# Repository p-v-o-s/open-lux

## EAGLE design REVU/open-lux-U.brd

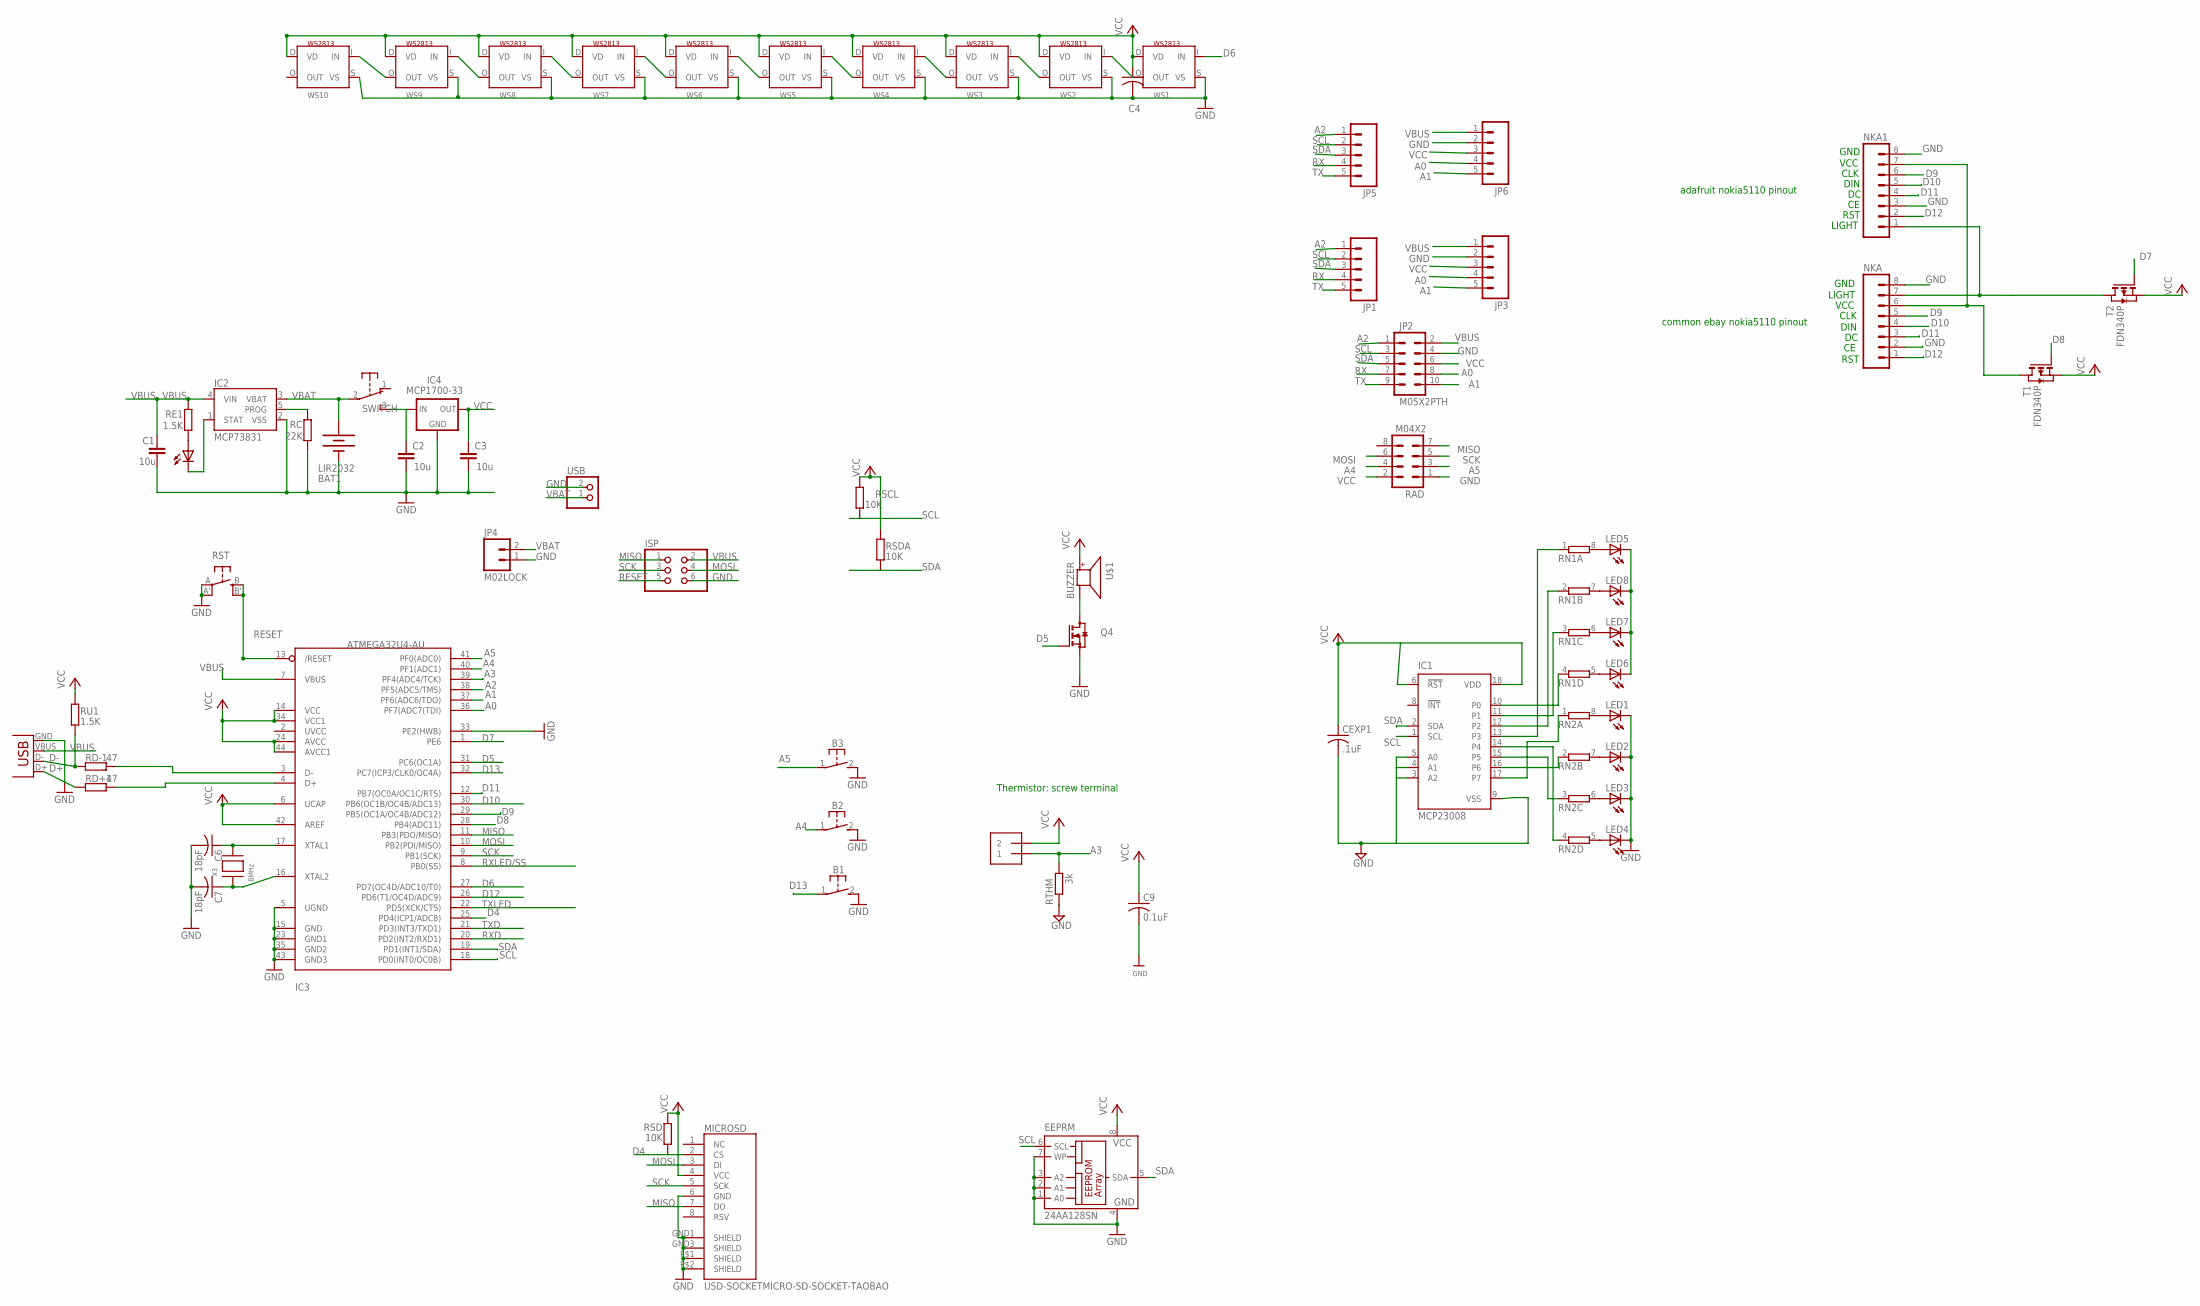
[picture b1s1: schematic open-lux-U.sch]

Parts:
B1, B2, B3: 31-XX; B3F-31XX
BAT1: LIR2032; BATTCOM_20MM_PTH_SMT
C1, C2, C3: 10u; C0805
C4: C-USC0805K; C0805K
C6, C7: 18pF; C0805K
C9: 0.1uF; C0805
CEXP1: .1uF; C0805K
EEPRM: 24AA128SN; SO-08
IC1: MCP23008; SO18W
IC2: MCP73831; SOT23-5
IC3: ATMEGA32U4-AU; TQFP44
IC4: MCP1700-33; SOT23
ISP: PINHD-2X3; 2X03
JP1, JP3, JP5, JP6: M05LOCK; 1X05_LOCK
JP2: M05X2PTH; AVR_ICSP
JP4: M02LOCK; 1X02_LOCK
LED1, LED2, LED3, LED4, LED5, LED6, LED7, LED8: LED3MM
MICROSD: USD-SOCKETMICRO-SD-SOCKET-TAOBAO; MICRO-SD-SOCKET-TAOBAO
NKA, NKA1: M08LOCK; 1X08_LOCK
PWR: 0805; CHIPLED_0805
Q4: BSS123; SOT23
RAD: M04X2; 2X4
RC: 22K; R0805
RD+1: 47; R0805
RD-1: 47; R0805
RE1: 1.5K; R0805
RN1, RN2: 4R-NEXB38V; EXB38V
RSCL: 10K; R0805
RSD: 10K; R0805
RSDA: 10K; R0805
RST: EVQQ2; EVQ-Q2
RTHM: 3k; 0204/7
RU1: 1.5K; R0805
SWITCH: EG1206
T1, T2: FDN340P; SOT-23
THM1: 1X2-3.5MM
U$1: BUZZER; SMT-8585-BUZZER
USB: JST_2PIN-SMT-RA; JST-PH-2-SMT-RA
WS1, WS2, WS3, WS4, WS5, WS6, WS7, WS8, WS9, WS10: WS2813; RGBLED5050_4
X2: USBSMD; USB-MINIB
X3: 8MHz; NX5032

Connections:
A0: IC3.36 (PF7(ADC7(TDI)), JP2.8, JP3.4, JP6.4
A1: IC3.37 (PF6(ADC6/TDO)), JP2.10, JP3.5, JP6.5
A2: IC3.38 (PF5(ADC5/TMS)), JP1.1, JP2.1, JP5.1
A3: IC3.39 (PF4(ADC4/TCK)), RTHM.2, THM1.1
A4: B2.1, IC3.40 (PF1(ADC1)), RAD.4
A5: B3.1, IC3.41 (PF0(ADC0)), RAD.3
D4: IC3.25 (PD4(ICP1/ADC8)), MICROSD.2 (CS), RSD.1
D5: IC3.31 (PC6(OC1A)), Q4.1 (G)
D6: IC3.27 (PD7(OC4D/ADC10/T0)), WS1.I (IN)
D7: IC3.1 (PE6), T2.3 (G)
D8: IC3.28 (PB4(ADC11)), T1.3 (G)
D9: IC3.29 (PB5(OC1A/OC4B/ADC12)), NKA.5, NKA1.6
D10: IC3.30 (PB6(OC1B/OC4B/ADC13)), NKA.4, NKA1.5
D11: IC3.12 (PB7(OC0A/OC1C/RTS)), NKA.3, NKA1.4
D12: IC3.26 (PD6(T1/OC4D/ADC9)), NKA.1, NKA1.2
D13: B1.1, IC3.32 (PC7(ICP3/CLK0/OC4A))
D+: RD+1.1, X2.D+
D-: RD-1.1, RU1.1, X2.D-
GND: B1.2 (S), B2.2 (S), B3.2 (S), BAT1.P$1 (-), C1.2, C2.2, C3.2, C4.2, C6.2, C7.2, C9.2, CEXP1.2, EEPRM.1 (A0), EEPRM.2 (A1), EEPRM.3 (A2), EEPRM.4 (GND), EEPRM.7 (WP), IC1.3 (A2), IC1.4 (A1), IC1.5 (A0), IC1.9 (VSS), IC2.2 (VSS), IC3.5 (UGND), IC3.15 (GND), IC3.23 (GND1), IC3.33 (PE2(HWB)), IC3.35 (GND2), IC3.43 (GND3), IC4.1 (GND), ISP.6, JP2.4, JP3.2, JP4.1, JP6.2, LED1.K (C), LED2.K (C), LED3.K (C), LED4.K (C), MICROSD.6 (GND), MICROSD.GND1 (SHIELD), MICROSD.GND3 (SHIELD), MICROSD.P$1 (SHIELD), MICROSD.P$2 (SHIELD), NKA.2, NKA.8, NKA1.3, NKA1.8, Q4.2 (S), RAD.1, RC.1, RST.A, RST.A' (P1), RTHM.1, USB.2 (1), WS1.S (VS), WS2.S (VS), WS3.S (VS), WS4.S (VS), WS5.S (VS), WS6.S (VS), WS7.S (VS), WS8.S (VS), WS9.S (VS), WS10.S (VS), X2.GND
MISO: IC3.11 (PB3(PDO/MISO)), ISP.1, MICROSD.7 (DO), RAD.7
MOSI: IC3.10 (PB2(PDI/MISO)), ISP.4, MICROSD.3 (DI), RAD.6
unnamed: C2.1, IC4.3 (IN), SWITCH.3 (S)
unnamed: C7.1, IC3.16 (XTAL2), X3.P$1
unnamed: C6.1, IC3.17 (XTAL1), X3.P$2
unnamed: WS9.O (OUT), WS10.I (IN)
unnamed: IC2.1 (STAT), PWR.C
unnamed: IC2.5 (PROG), RC.2
unnamed: Q4.3 (D), U$1.-
unnamed: IC1.14 (P4), RN2.4 (1)
unnamed: PWR.A, RE1.1
unnamed: IC1.15 (P5), RN2.3 (1)
unnamed: NKA.7, NKA1.1
unnamed: IC1.16 (P6), RN2.2 (1)
unnamed: WS6.O (OUT), WS7.I (IN)
unnamed: IC1.17 (P7), RN2.1
unnamed: LED1.A, RN2.8 (2)
unnamed: LED2.A, RN2.7 (2)
unnamed: WS4.O (OUT), WS5.I (IN)
unnamed: WS5.O (OUT), WS6.I (IN)
unnamed: IC3.4 (D+), RD+1.2
unnamed: IC3.3 (D-), RD-1.2
unnamed: WS1.O (OUT), WS2.I (IN)
unnamed: WS2.O (OUT), WS3.I (IN)
unnamed: WS3.O (OUT), WS4.I (IN)
unnamed: LED3.A, RN2.6 (2)
unnamed: WS8.O (OUT), WS9.I (IN)
unnamed: WS7.O (OUT), WS8.I (IN)
unnamed: LED4.A, RN2.5 (2)
unnamed: LED5.K (C), LED6.K (C), LED7.K (C), LED8.K (C)
unnamed: NKA.6, NKA1.7, T1.1 (D)
unnamed: LED5.A, RN1.8 (2)
unnamed: LED6.A, RN1.5 (2)
unnamed: LED7.A, RN1.6 (2)
unnamed: LED8.A, RN1.7 (2)
unnamed: IC1.13 (P3), RN1.1
unnamed: IC1.12 (P2), RN1.2 (1)
unnamed: IC1.11 (P1), RN1.3 (1)
unnamed: IC1.10 (P0), RN1.4 (1)
RESET: IC3.13 (/RESET), ISP.5, RST.B (S), RST.B' (S1)
RX: JP1.4, JP2.7, JP5.4
RXD: IC3.20 (PD2(INT2/RXD1))
RXLED/SS: IC3.8 (PB0(SS))
SCK: IC3.9 (PB1(SCK)), ISP.3, MICROSD.5 (SCK), RAD.5
SCL: EEPRM.6 (SCL), IC1.1 (SCL), IC3.18 (PD0(INT0/OC0B)), JP1.2, JP2.3, JP5.2, RSCL.1
SDA: EEPRM.5 (SDA), IC1.2 (SDA), IC3.19 (PD1(INT1/SDA)), JP1.3, JP2.5, JP5.3, RSDA.1
TX: JP1.5, JP2.9, JP5.5
TXD: IC3.21 (PD3(INT3/TXD1))
TXLED: IC3.22 (PD5(XCK/CTS))
VBAT: BAT1.P$2 (+), IC2.3 (VBAT), JP4.2, SWITCH.2, USB.1 (2)
VBUS: C1.1, IC2.4 (VIN), IC3.7 (VBUS), ISP.2, JP2.2, JP3.1, JP6.1, RE1.2, X2.VBUS
VCC: C3.1, C4.1, C9.1, CEXP1.1, EEPRM.8 (VCC), IC1.6 (!RST), IC1.18 (VDD), IC3.6 (UCAP), IC3.14 (VCC), IC3.24 (AVCC), IC3.34 (VCC1), IC3.42 (AREF), IC3.44 (AVCC1), IC4.2 (OUT), JP2.6, JP3.3, JP6.3, MICROSD.4 (VCC), RAD.2, RSCL.2, RSD.2, RSDA.2, RU1.2, T1.2 (S), T2.2 (S), THM1.2, U$1.+, WS1.D (VD), WS2.D (VD), WS3.D (VD), WS4.D (VD), WS5.D (VD), WS6.D (VD), WS7.D (VD), WS8.D (VD), WS9.D (VD), WS10.D (VD)

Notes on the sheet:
RST
DIN
CLK
VCC
LIGHT
GND
adafruit nokia5110 pinout
common ebay nokia5110 pinout
Thermistor: screw terminal

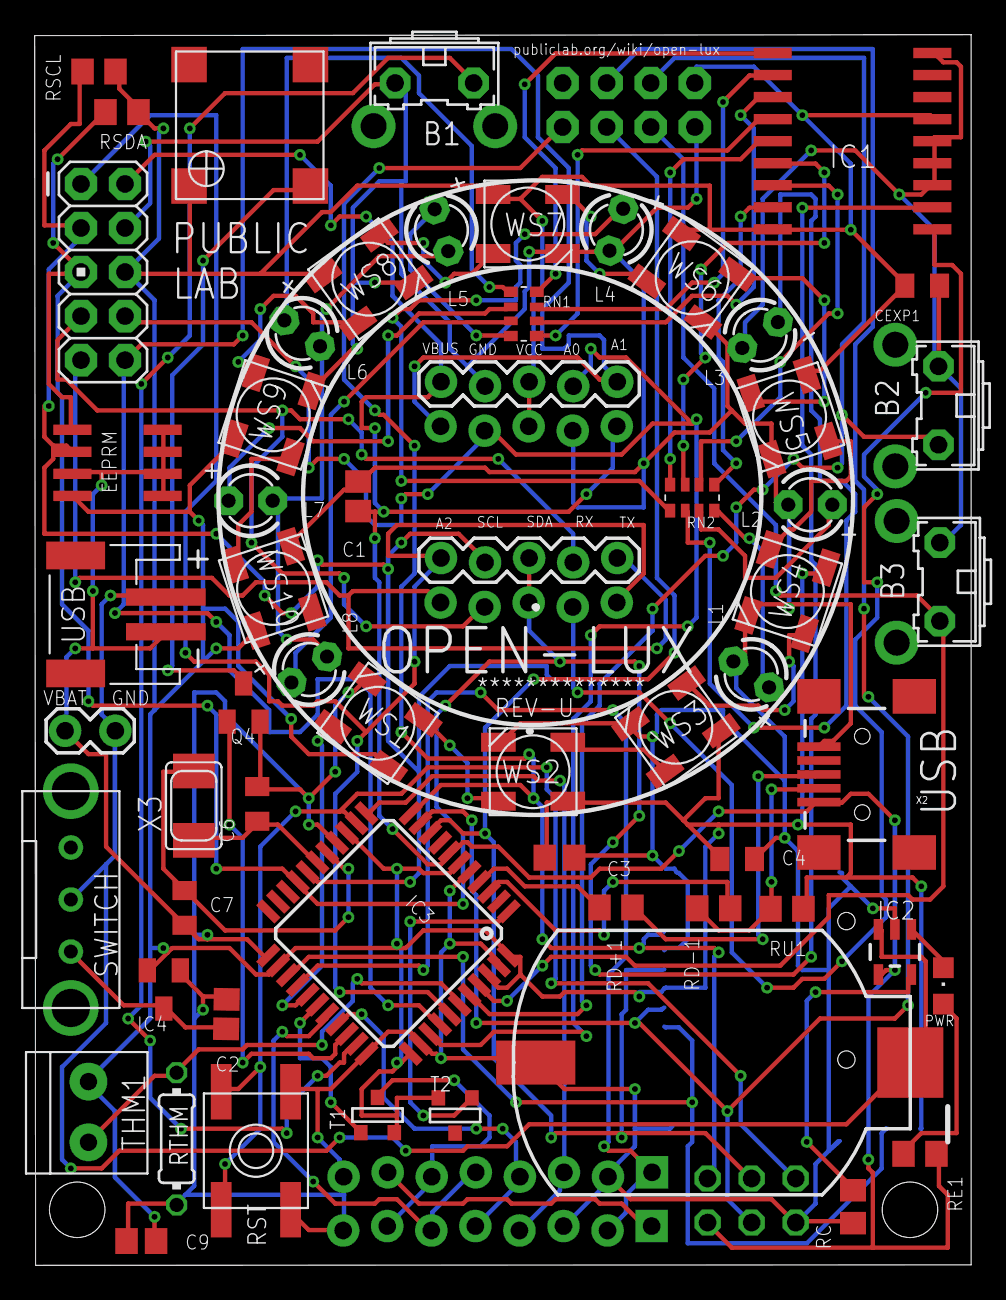
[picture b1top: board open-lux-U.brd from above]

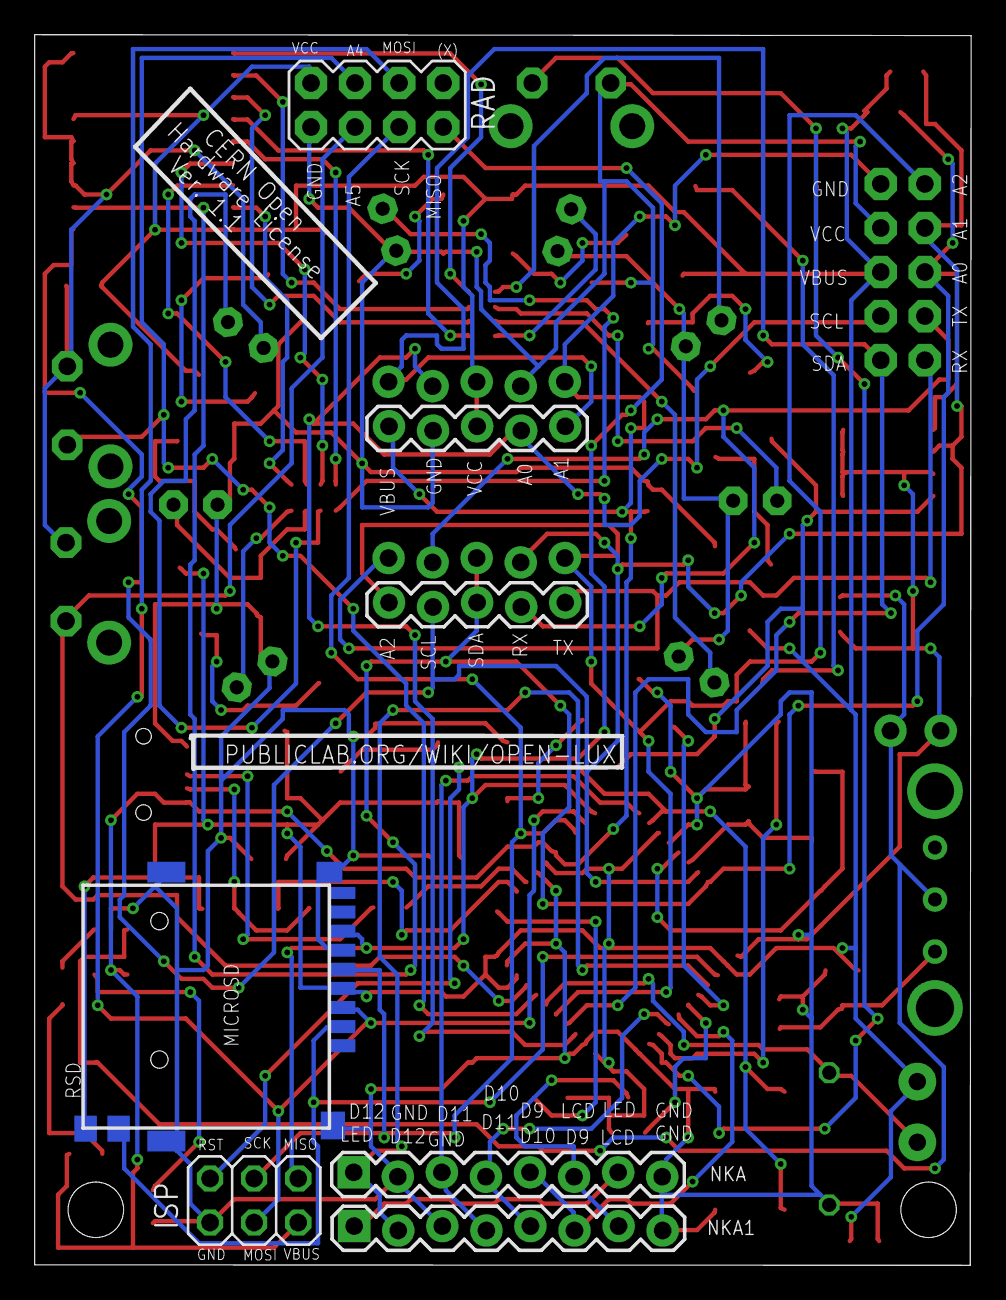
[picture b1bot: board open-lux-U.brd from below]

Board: 2 copper layers, 54.0 x 70.9 mm, 68 parts (8 on the bottom side), 67 nets.

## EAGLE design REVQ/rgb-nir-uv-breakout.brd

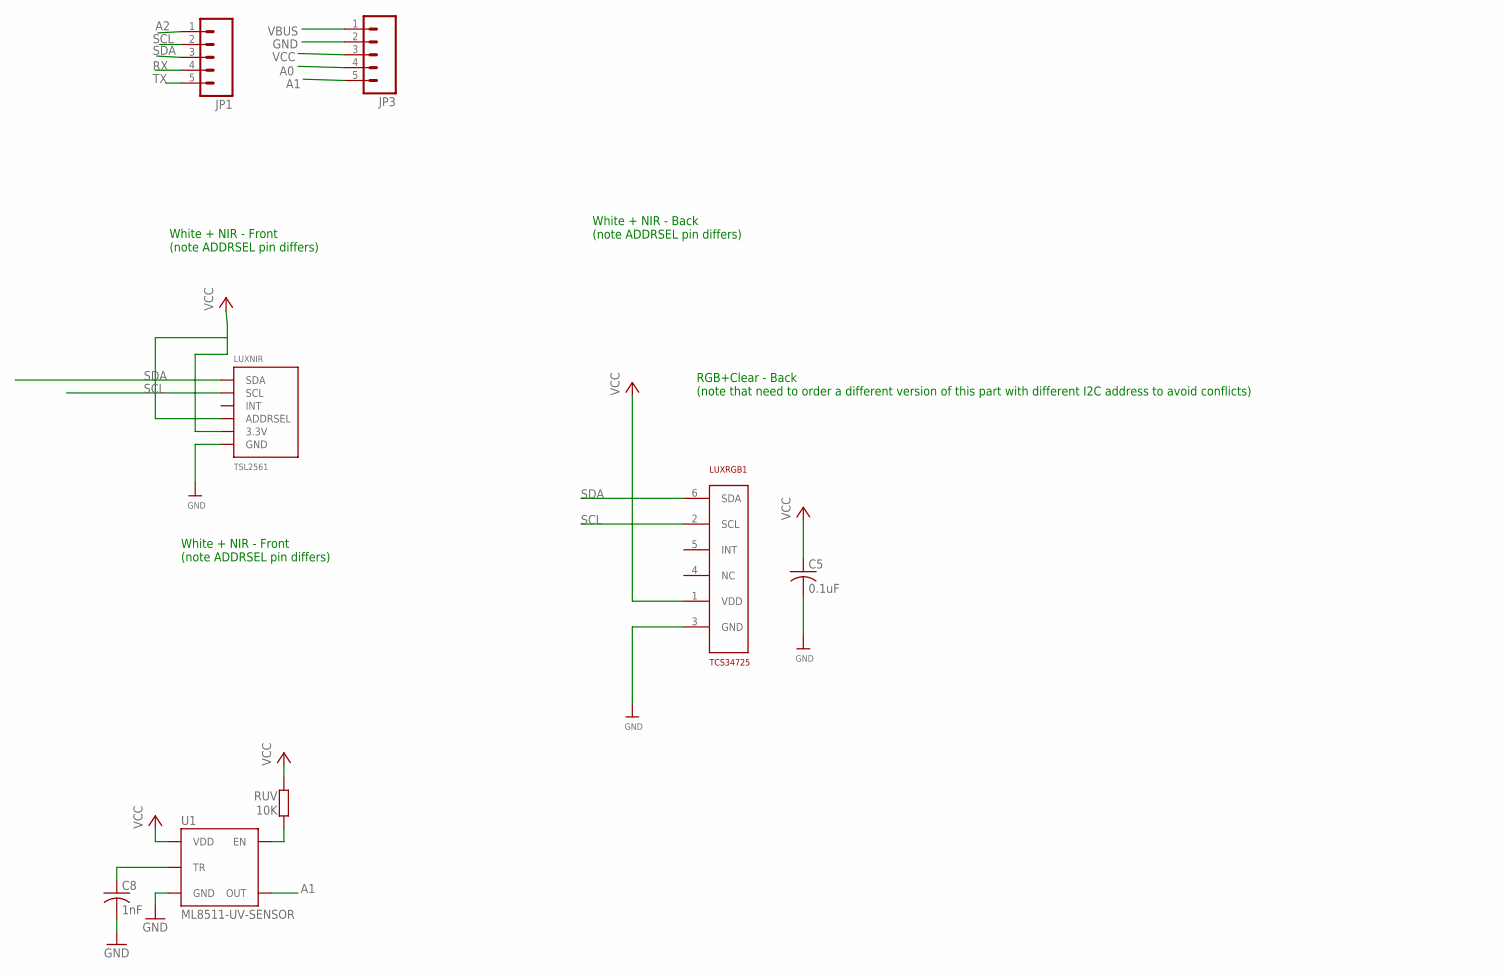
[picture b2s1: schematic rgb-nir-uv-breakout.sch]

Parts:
C5: 0.1uF; C0805
C8: 1nF; C0805
JP1, JP3: M05LOCK; 1X05_LOCK
LUXNIR: TSL2561; TSL2561_FN@1
LUXRGB1: TCS34725; DFN-6
RUV: 10K; R0805
U1: ML8511-UV-SENSOR; ML8511

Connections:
A0: JP3.4
A1: JP3.5, U1.8 (OUT)
A2: JP1.1
ENABLE: RUV.1, U1.4 (EN)
GND: C5.2, C8.2, JP3.2, LUXNIR.VSS (GND), LUXRGB1.3 (GND), U1.5 (GND)
unnamed: C8.1, U1.10 (TR)
RX: JP1.4
SCL: JP1.2, LUXNIR.CLK (SCL), LUXRGB1.2 (SCL)
SDA: JP1.3, LUXNIR.DATA (SDA), LUXRGB1.6 (SDA)
TX: JP1.5
VBUS: JP3.1
VCC: C5.1, JP3.3, LUXNIR.ADR (ADDRSEL), LUXNIR.VDD (3.3V), LUXRGB1.1 (VDD), RUV.2, U1.7 (VDD)

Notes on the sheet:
White + NIR - Front (note ADDRSEL pin differs)
White + NIR - Back (note ADDRSEL pin differs)
RGB+Clear - Back (note that need to order a different version of this part with different I2C address to avoid conflicts)

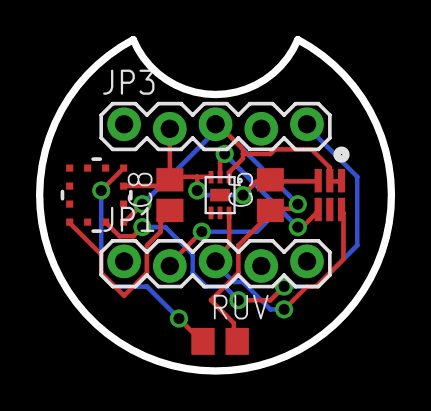
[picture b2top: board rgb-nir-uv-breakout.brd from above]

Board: 2 copper layers, 19.5 x 18.4 mm, 8 parts (0 on the bottom side), 7 nets.

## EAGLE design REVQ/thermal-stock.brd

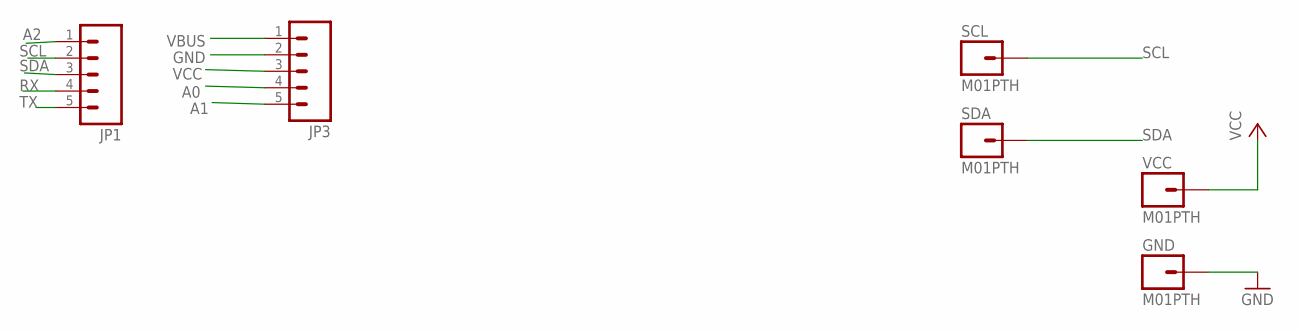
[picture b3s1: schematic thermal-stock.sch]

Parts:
GND: M01PTH; 1X01
JP1, JP3: M05LOCK; 1X05_LOCK
SCL: M01PTH; 1X01
SDA: M01PTH; 1X01
VCC: M01PTH; 1X01

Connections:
A0: JP3.4
A1: JP3.5
A2: JP1.1
GND: GND.1, JP3.2
RX: JP1.4
SCL: JP1.2, SCL.1
SDA: JP1.3, SDA.1
TX: JP1.5
VBUS: JP3.1
VCC: JP3.3, VCC.1

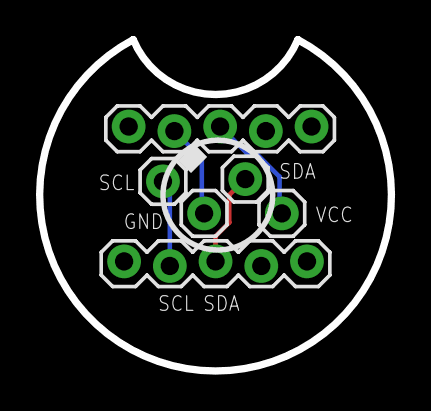
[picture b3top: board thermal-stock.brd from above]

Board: 2 copper layers, 19.5 x 18.4 mm, 6 parts (0 on the bottom side), 4 nets.

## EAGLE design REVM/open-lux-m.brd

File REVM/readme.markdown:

This is intended to have headers appropriate for the Adafruit Nokia 5110 breakout board.

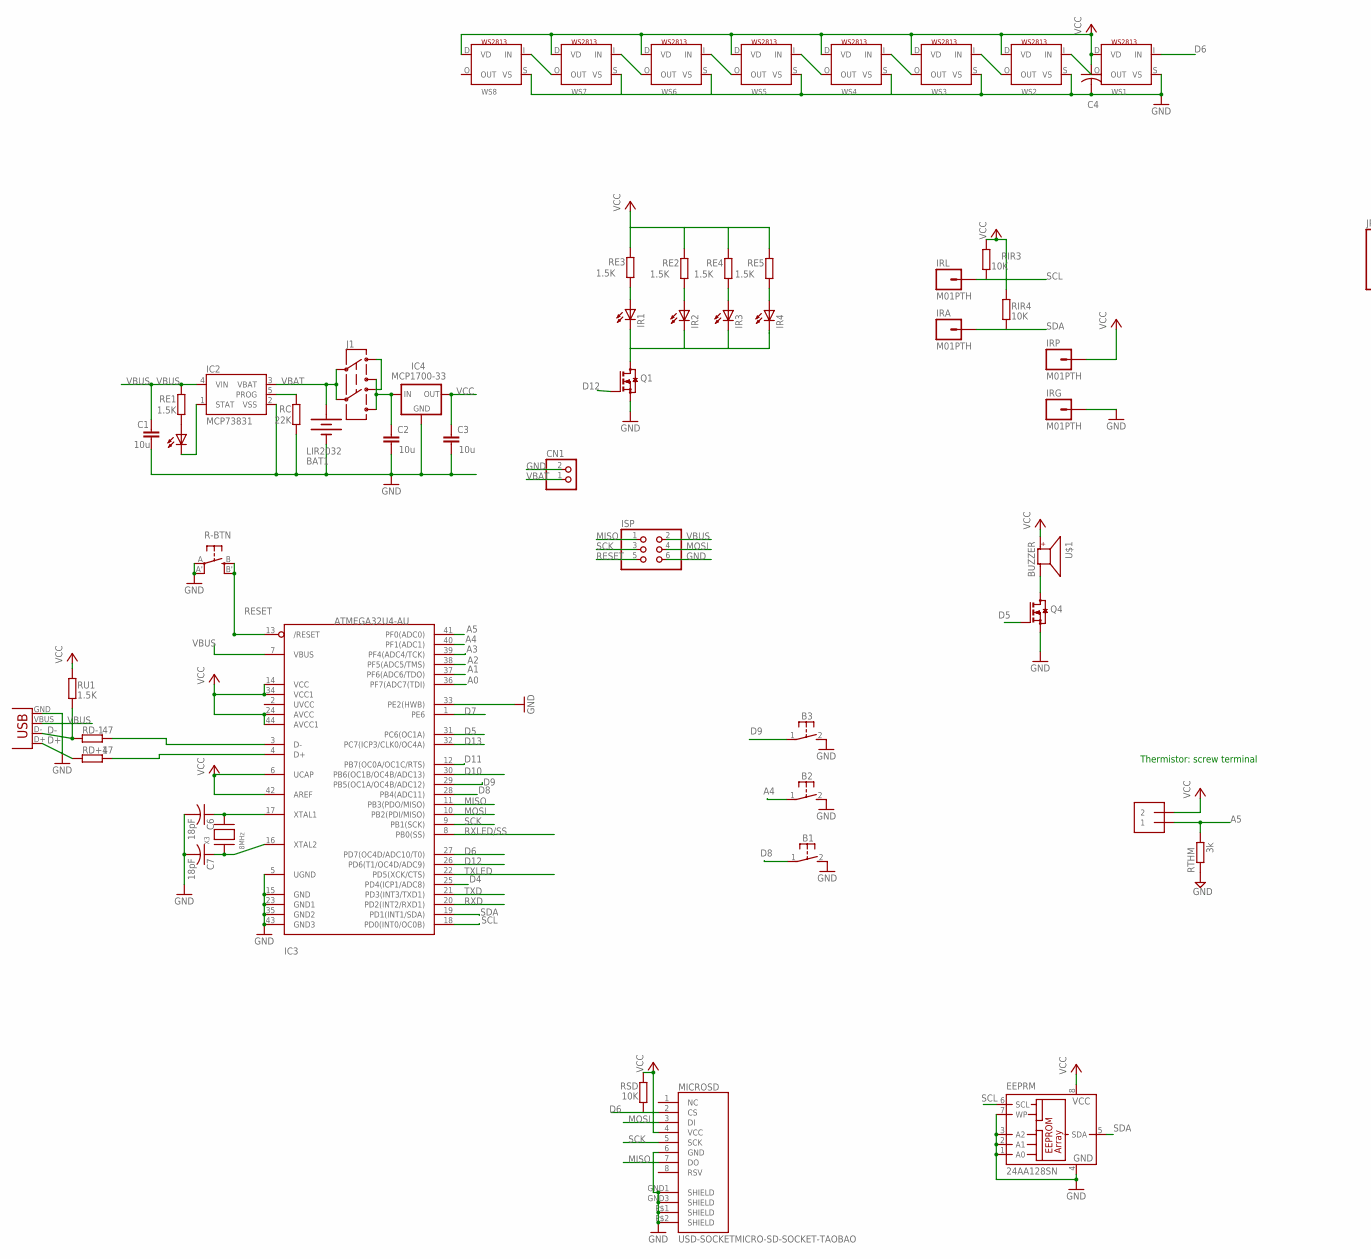
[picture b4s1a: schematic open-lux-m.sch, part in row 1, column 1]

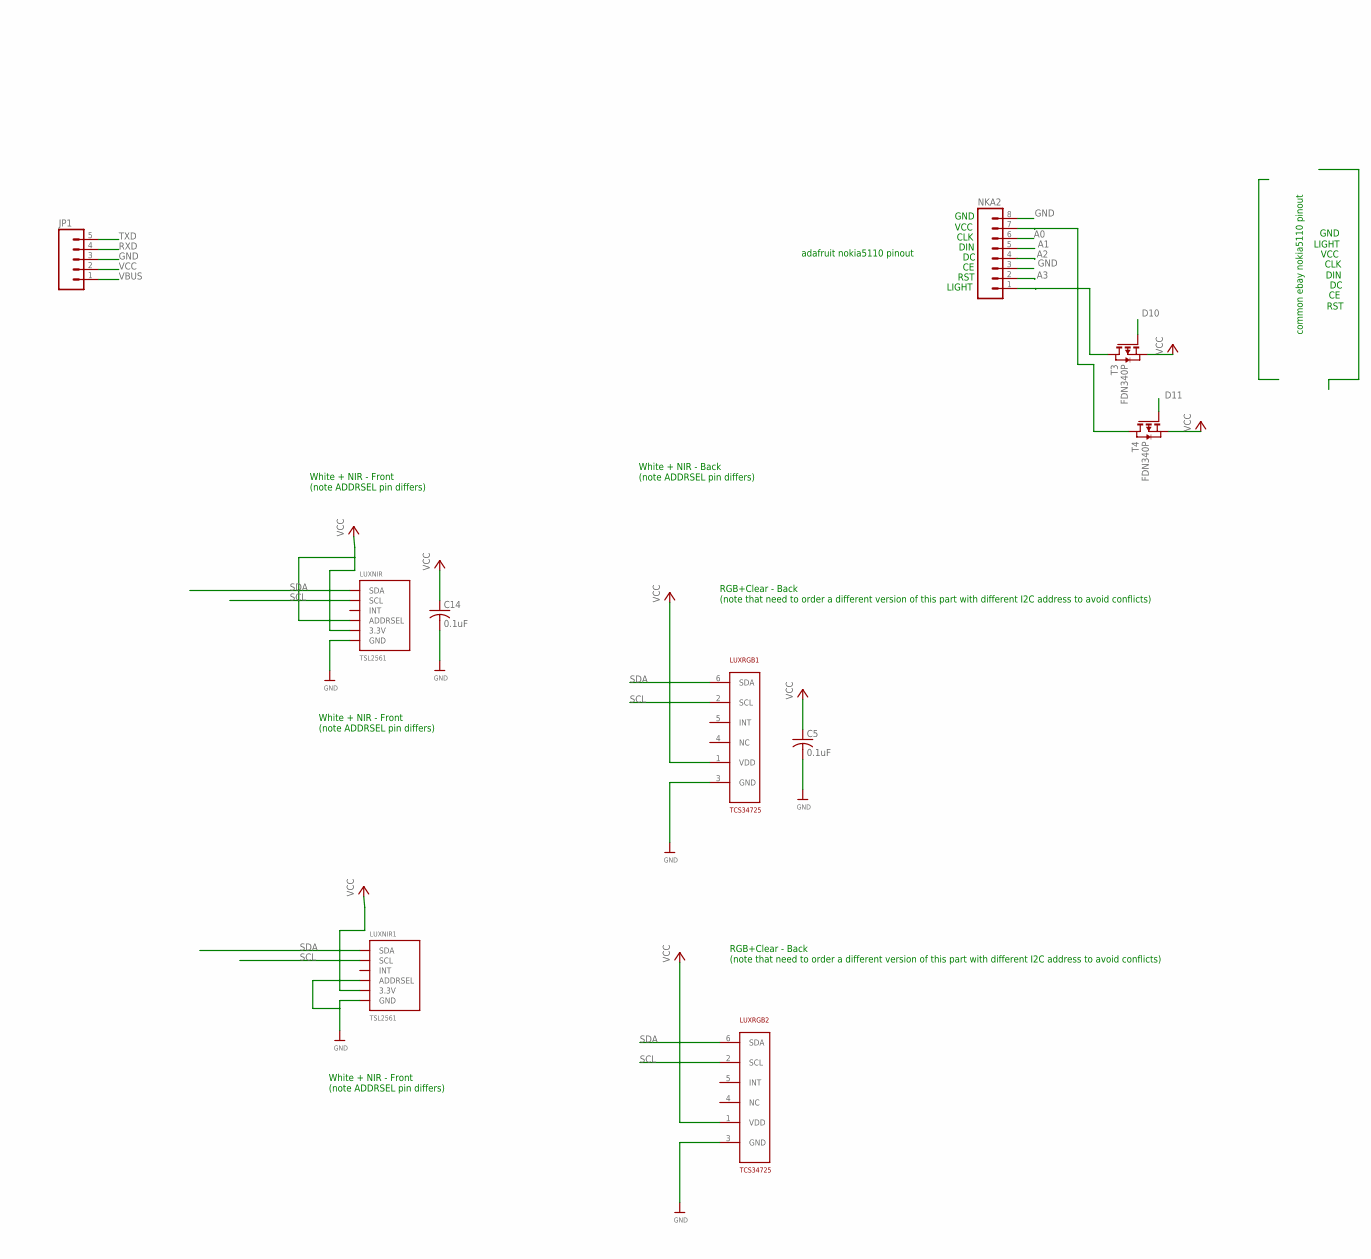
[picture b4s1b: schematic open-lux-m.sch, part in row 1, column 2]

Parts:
B1, B2, B3: 31-XX; B3F-31XX
BAT1: LIR2032; BATTCOM_20MM_PTH_SMT
C1, C2, C3: 10u; C0805
C4: C-USC0805K; C0805K
C5, C14: 0.1uF; C0805
C6, C7: 18pF; C0805K
CHARGE: 0805; CHIPLED_0805
CN1: JST_2PIN-SMT-RA; JST-PH-2-SMT-RA
EEPRM: 24AA128SN; SO-08
IC2: MCP73831; SOT23-5
IC3: ATMEGA32U4-AU; TQFP44
IC4: MCP1700-33; SOT23
IR1, IR2, IR3, IR4: LEDCHIP-LED0603; CHIP-LED0603
IRA: M01PTH; 1X01
IRG: M01PTH; 1X01
IRL: M01PTH; 1X01
IRP: M01PTH; 1X01
ISP: PINHD-2X3; 2X03
J1: AYZ0202
JP1: M05LOCK; 1X05_LOCK
LUXNIR, LUXNIR1: TSL2561; TSL2561_FN@1
LUXRGB1, LUXRGB2: TCS34725; DFN-6
MICROSD: USD-SOCKETMICRO-SD-SOCKET-TAOBAO; MICRO-SD-SOCKET-TAOBAO
NKA2: M08LOCK; 1X08_LOCK
Q1, Q4: BSS123; SOT23
R-BTN: EVQQ2; EVQ-Q2
RC: 22K; R0805
RD+1: 47; R0805
RD-1: 47; R0805
RE1, RE2, RE3, RE4, RE5: 1.5K; R0805
RIR3, RIR4: 10K; R0805
RSD: 10K; R0805
RTHM: 3k; 0204/7
RU1: 1.5K; R0805
T3, T4: FDN340P; SOT-23
THM1: 1X2-3.5MM
U$1: BUZZER; SMT-8585-BUZZER
WS1, WS2, WS3, WS4, WS5, WS6, WS7, WS8: WS2813; RGBLED5050_4
X2: USBSMD; USB-MINIB
X3: 8MHz; NX5032

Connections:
A0: IC3.36 (PF7(ADC7(TDI)), NKA2.6
A1: IC3.37 (PF6(ADC6/TDO)), NKA2.5
A2: IC3.38 (PF5(ADC5/TMS))
A3: IC3.39 (PF4(ADC4/TCK)), NKA2.2
A4: B2.1, IC3.40 (PF1(ADC1))
A5: IC3.41 (PF0(ADC0)), RTHM.2, THM1.1
D4: IC3.25 (PD4(ICP1/ADC8))
D5: IC3.31 (PC6(OC1A)), Q4.1 (G)
D6: IC3.27 (PD7(OC4D/ADC10/T0)), MICROSD.2 (CS), RSD.1, WS1.I (IN)
D7: IC3.1 (PE6)
D8: B1.1, IC3.28 (PB4(ADC11))
D9: B3.1, IC3.29 (PB5(OC1A/OC4B/ADC12))
D10: IC3.30 (PB6(OC1B/OC4B/ADC13)), T3.3 (G)
D11: IC3.12 (PB7(OC0A/OC1C/RTS)), T4.3 (G)
D12: IC3.26 (PD6(T1/OC4D/ADC9)), Q1.1 (G)
D13: IC3.32 (PC7(ICP3/CLK0/OC4A))
D+: RD+1.1, X2.D+
D-: RD-1.1, RU1.1, X2.D-
GND: B1.2 (S), B2.2 (S), B3.2 (S), BAT1.P$1 (-), C1.2, C2.2, C3.2, C4.2, C5.2, C6.2, C7.2, C14.2, CN1.2 (1), EEPRM.1 (A0), EEPRM.2 (A1), EEPRM.3 (A2), EEPRM.4 (GND), EEPRM.7 (WP), IC2.2 (VSS), IC3.5 (UGND), IC3.15 (GND), IC3.23 (GND1), IC3.33 (PE2(HWB)), IC3.35 (GND2), IC3.43 (GND3), IC4.1 (GND), IRG.1, ISP.6, JP1.3, LUXNIR.VSS (GND), LUXNIR1.ADR (ADDRSEL), LUXNIR1.VSS (GND), LUXRGB1.3 (GND), LUXRGB2.3 (GND), MICROSD.6 (GND), MICROSD.GND1 (SHIELD), MICROSD.GND3 (SHIELD), MICROSD.P$1 (SHIELD), MICROSD.P$2 (SHIELD), NKA2.3, NKA2.8, Q1.2 (S), Q4.2 (S), R-BTN.A, R-BTN.A' (P1), RC.1, RTHM.1, WS1.S (VS), WS2.S (VS), WS3.S (VS), WS4.S (VS), X2.GND
GND1: WS6.S (VS)
GND2: WS5.S (VS)
MISO: IC3.11 (PB3(PDO/MISO)), ISP.1, MICROSD.7 (DO)
MOSI: IC3.10 (PB2(PDI/MISO)), ISP.4, MICROSD.3 (DI)
unnamed: J1.3 (1), J1.6 (4)
unnamed: C7.1, IC3.16 (XTAL2), X3.P$1
unnamed: C6.1, IC3.17 (XTAL1), X3.P$2
unnamed: CHARGE.C, IC2.1 (STAT)
unnamed: IC2.5 (PROG), RC.2
unnamed: Q4.3 (D), U$1.-
unnamed: IR1.C, IR2.C, IR3.C, IR4.C, Q1.3 (D)
unnamed: CHARGE.A, RE1.1
unnamed: IR1.A, RE3.1
unnamed: NKA2.1, T3.1 (D)
unnamed: IR2.A, RE2.1
unnamed: WS6.O (OUT), WS7.I (IN)
unnamed: IR3.A, RE4.1
unnamed: WS7.S (VS), WS8.S (VS)
unnamed: IR4.A, RE5.1
unnamed: WS5.O (OUT), WS6.I (IN)
unnamed: IC3.4 (D+), RD+1.2
unnamed: IC3.3 (D-), RD-1.2
unnamed: WS1.O (OUT), WS2.I (IN)
unnamed: WS2.O (OUT), WS3.I (IN)
unnamed: WS3.O (OUT), WS4.I (IN)
unnamed: WS7.O (OUT), WS8.I (IN)
unnamed: NKA2.7, T4.1 (D)
RESET: IC3.13 (/RESET), ISP.5, R-BTN.B (S), R-BTN.B' (S1)
RXD: IC3.20 (PD2(INT2/RXD1)), JP1.4
RXLED/SS: IC3.8 (PB0(SS))
SCK: IC3.9 (PB1(SCK)), ISP.3, MICROSD.5 (SCK)
SCL: EEPRM.6 (SCL), IC3.18 (PD0(INT0/OC0B)), IRL.1, LUXNIR.CLK (SCL), LUXNIR1.CLK (SCL), LUXRGB1.2 (SCL), LUXRGB2.2 (SCL), RIR3.1
SDA: EEPRM.5 (SDA), IC3.19 (PD1(INT1/SDA)), IRA.1, LUXNIR.DATA (SDA), LUXNIR1.DATA (SDA), LUXRGB1.6 (SDA), LUXRGB2.6 (SDA), RIR4.1
TXD: IC3.21 (PD3(INT3/TXD1)), JP1.5
TXLED: IC3.22 (PD5(XCK/CTS))
VBAT: BAT1.P$2 (+), CN1.1 (2), IC2.3 (VBAT), J1.2, J1.5
VBUS: C1.1, IC2.4 (VIN), IC3.7 (VBUS), ISP.2, JP1.1, RE1.2, X2.VBUS
VCC: C3.1, C4.1, C5.1, C14.1, EEPRM.8 (VCC), IC3.6 (UCAP), IC3.14 (VCC), IC3.24 (AVCC), IC3.34 (VCC1), IC3.42 (AREF), IC3.44 (AVCC1), IC4.2 (OUT), IRP.1, JP1.2, LUXNIR.ADR (ADDRSEL), LUXNIR.VDD (3.3V), LUXNIR1.VDD (3.3V), LUXRGB1.1 (VDD), LUXRGB2.1 (VDD), MICROSD.4 (VCC), RE2.2, RE3.2, RE4.2, RE5.2, RIR3.2, RIR4.2, RSD.2, RU1.2, T3.2 (S), T4.2 (S), THM1.2, U$1.+, WS1.D (VD), WS2.D (VD), WS3.D (VD), WS4.D (VD), WS5.D (VD), WS6.D (VD), WS7.D (VD), WS8.D (VD)
VDD: C2.1, IC4.3 (IN), J1.1 (3), J1.4 (6)

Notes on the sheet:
White + NIR - Front (note ADDRSEL pin differs)
RST
DIN
CLK
VCC
LIGHT
GND
Thermistor: screw terminal
White + NIR - Back (note ADDRSEL pin differs)
RGB+Clear - Back (note that need to order a different version of this part with different I2C address to avoid conflicts)
adafruit nokia5110 pinout
common ebay nokia5110 pinout

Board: 2 copper layers, 65 parts (7 on the bottom side), 50 nets, no tracks yet.

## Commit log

2014-04-07 got OSH Park estimate
2014-04-20 prettified
2014-04-20 fully routed
2014-04-21 fully routed, no DRC errors.

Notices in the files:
REVU/open-lux-U.brd:
Hardware License
parts and their libraries:
microbuilder: This work is placed in the public domain, and may be freely used for commercial and non-commercial work with the following conditions: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
SparkFun-Connectors: Licensing: Creative Commons ShareAlike 4.0 International - https://creativecommons.org/licenses/by-sa/4.0
